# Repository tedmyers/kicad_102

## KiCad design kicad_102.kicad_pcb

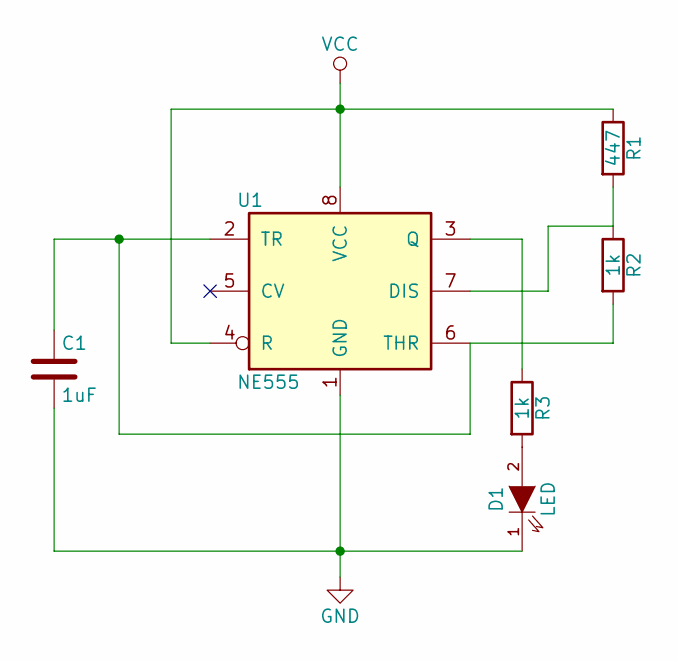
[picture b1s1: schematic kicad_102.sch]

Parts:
C1: 1uF; C_0603_HandSoldering
D1: LED; LED-8MM
R1: 447; Resistor_Horizontal_RM10mm
R2, R3: 1k; Resistor_Horizontal_RM10mm
U1: NE555; DIP-8_W7.62mm

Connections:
GND: C1.2, D1.1 (K), U1.1 (GND)
unnamed: C1.1, R2.2, U1.2 (TR), U1.6 (THR)
unnamed: D1.2 (A), R3.2
unnamed: R1.2, R2.1, U1.7 (DIS)
unnamed: R3.1, U1.3 (Q)
VCC: R1.1, U1.4 (R), U1.8 (VCC)

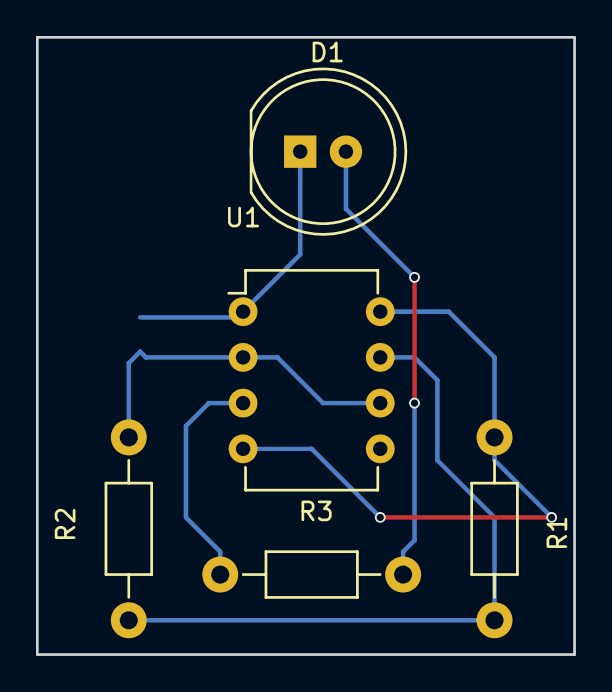
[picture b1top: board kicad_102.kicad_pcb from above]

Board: 2 copper layers, 29.8 x 34.3 mm, 6 parts (1 on the bottom side), 6 nets.

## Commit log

2016-11-03 Initial commit
    File names should still be changed
2016-11-03 Changed file names
2016-11-03 components associated
2016-11-03 netlist generated
2016-11-03 Components imported to pcbnew
2016-11-03 pcb finished
